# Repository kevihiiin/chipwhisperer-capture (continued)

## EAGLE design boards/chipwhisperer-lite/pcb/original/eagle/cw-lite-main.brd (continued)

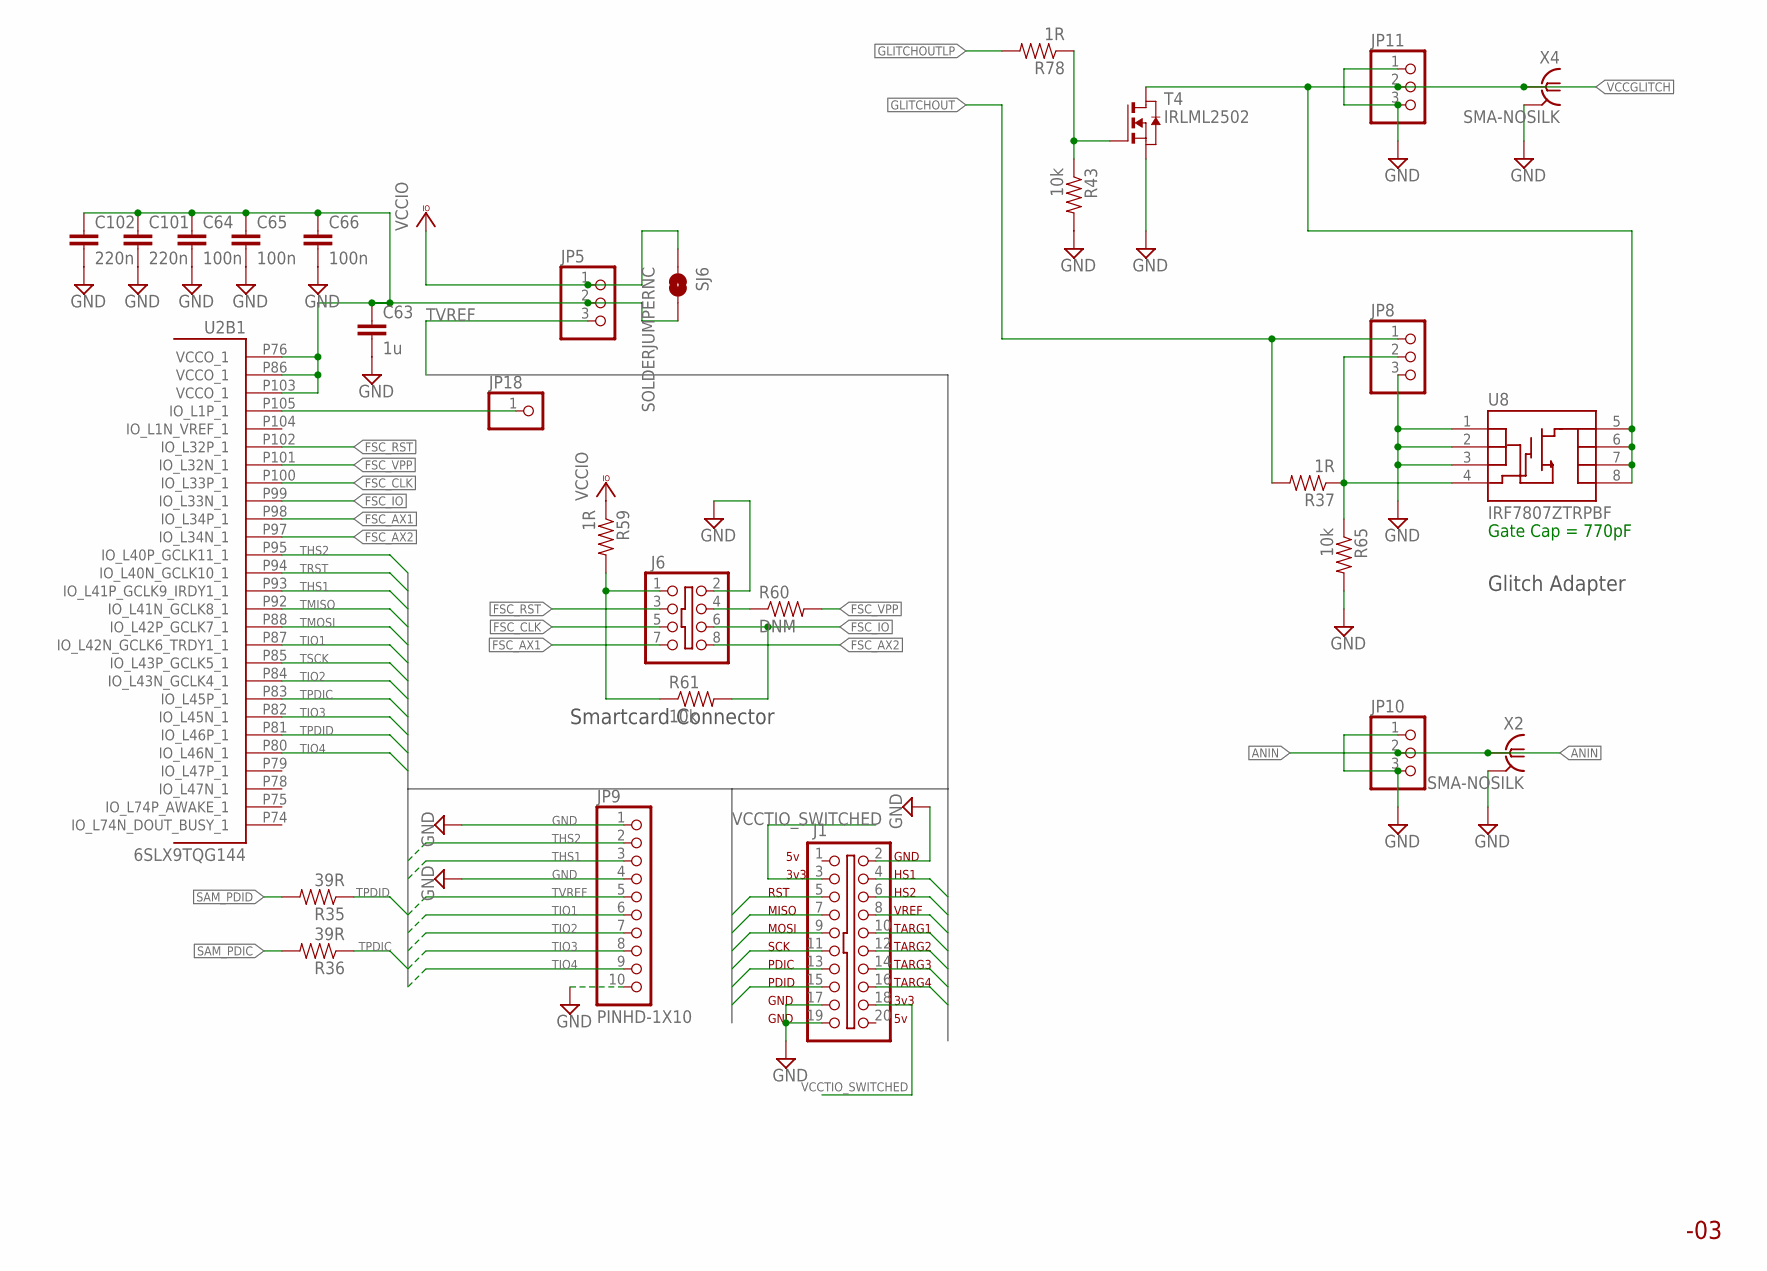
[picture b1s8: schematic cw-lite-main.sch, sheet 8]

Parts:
C63: 1u; 0603C
C64, C65, C66: 100n; 0402C
C101, C102: 220n; 0402C
J1: SHROUD_2X10-SHROUDED; PINSHRD_PTH_2X10
J6: SHROUD_2X4SHROUD; PINSHRD_PTH_2X04
JP5, JP8, JP10, JP11: PINHD-1X3; 1X03
JP9: PINHD-1X10; 1X10-BIG
JP18: PINHD-1X1; 1X01
R35, R36: 39R; 0603R
R37, R59, R78: 1R; 0603R
R43, R61, R65: 10k; 0603R
R60: DNM; 0603R
SJ6: SOLDERJUMPERNC; SJ_2S
T4: IRLML2502; SOT-23; MPN IRLML2502TRPBF
U2: 6SLX9TQG144; TQ144; MPN XC6SLX9-3TQG144C
U8: IRF7807ZTRPBF; SO08
X2, X4: SMA-NOSILK; J502-ND-142-0711-821/826-NOSILK

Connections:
ANIN: JP10.2, X2.1; also elsewhere on the board
FSC_AX1: J6.7, U2.P98 (IO_L34P_1)
FSC_AX2: J6.8, U2.P97 (IO_L34N_1)
FSC_CLK: J6.5, U2.P100 (IO_L33P_1)
FSC_IO: J6.6, R61.2, U2.P99 (IO_L33N_1)
FSC_RST: J6.3, U2.P102 (IO_L32P_1)
FSC_VPP: R60.2, U2.P101 (IO_L32N_1)
GLITCHOUT: JP8.1, R37.2; also elsewhere on the board
GLITCHOUTLP: R78.2; also elsewhere on the board
GND: C63.2, C64.2, C65.2, C66.2, C101.2, C102.2, J1.2, J1.17, J1.19, J6.2, JP8.3, JP9.1, JP9.4, JP9.10, JP10.1, JP10.3, JP11.1, JP11.3, R43.2, R65.2, T4.2 (S), U8.1 (S), U8.2 (S), U8.3 (S), X2.G@1 (2), X2.G@2 (2), X2.G@3 (2), X2.G@4 (2), X4.G@1 (2), X4.G@2 (2), X4.G@3 (2), X4.G@4 (2); also elsewhere on the board
unnamed: JP8.2, R37.1, R65.1, U8.4 (G)
unnamed: JP18.1, U2.P105 (IO_L1P_1)
unnamed: R43.1, R78.1, T4.3 (G)
unnamed: J6.1, R59.2, R61.1
unnamed: J6.4, R60.1
SAM_PDIC: R36.2; also elsewhere on the board
SAM_PDID: R35.2; also elsewhere on the board
TARGET_VCCIO: C63.1, C64.1, C65.1, C66.1, C101.1, C102.1, JP5.2, SJ6.2, U2.P76 (VCCO_1), U2.P86 (VCCO_1), U2.P103 (VCCO_1)
THS1: J1.4, JP9.3, U2.P93 (IO_L41P_GCLK9_IRDY1_1); also elsewhere on the board
THS2: J1.6, JP9.2, U2.P95 (IO_L40P_GCLK11_1); also elsewhere on the board
TIO1: J1.10, JP9.6, U2.P87 (IO_L42N_GCLK6_TRDY1_1); also elsewhere on the board
TIO2: J1.12, JP9.7, U2.P84 (IO_L43N_GCLK4_1); also elsewhere on the board
TIO3: J1.14, JP9.8, U2.P82 (IO_L45N_1); also elsewhere on the board
TIO4: J1.16, JP9.9, U2.P80 (IO_L46N_1); also elsewhere on the board
TMISO: J1.7, U2.P92 (IO_L41N_GCLK8_1); also elsewhere on the board
TMOSI: J1.9, U2.P88 (IO_L42P_GCLK7_1); also elsewhere on the board
TPDIC: J1.13, R36.1, U2.P83 (IO_L45P_1); also elsewhere on the board
TPDID: J1.15, R35.1, U2.P81 (IO_L46P_1); also elsewhere on the board
TRST: J1.5, U2.P94 (IO_L40N_GCLK10_1); also elsewhere on the board
TSCK: J1.11, U2.P85 (IO_L43P_GCLK5_1); also elsewhere on the board
TVREF: J1.8, JP5.3, JP9.5; also elsewhere on the board
VCCGLITCH: JP11.2, T4.1 (D), U8.5 (D), U8.6 (D), U8.7 (D), U8.8 (D), X4.1; also elsewhere on the board
VCCIO: JP5.1, R59.1, SJ6.1; also elsewhere on the board
VCCTIO_SWITCHED: J1.3, J1.18; also elsewhere on the board

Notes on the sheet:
HS1
HS2
VREF
TARG1
TARG2
TARG3
TARG4
3v3
RST
MISO
MOSI
SCK
PDIC
PDID
GND
Glitch Adapter
Smartcard Connector
Gate Cap = 770pF

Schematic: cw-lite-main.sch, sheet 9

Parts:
C37: 47u; 0805
C103: 10u; 0603C
C104: 10n; 0603C
C105, C107: 1u; 0603C
C106, C108, C109: 100n; 0603C
C115, C116, C121: DNM; 0603C
C118, C119, C120: CAP0603-CAP; 0603C
J2: SHROUD_2X10-SHROUDED; PINSHRD_PTH_2X10
J9: 2171790001; MOLEX_2171790001
JP6, JP7, JP12: PINHD-1X2; 1X02
JP13: PINHD-1X9; 1X09-BIG
JP14, JP15, JP16, JP17: PINHD-1X1; 1X01
L10: 1k/500mA; FB603
LED9, LED10: LED-0603; LED-603
Q2: CRYSTALHC49U-V; HC49U-V
R13: 10k; 0603R
R66, R76: 49R9; 0805
R67, R72: 100R; 0603R
R73: DNM; 0603R
R74, R75: 1k; 0603R
R83, R84: 5k1; R0402
SJ2: SOLDERJUMPER_2WAYPASTE2&3; SJ_3_PASTE2&3
SJ3, SJ4, SJ5, SJ7: SOLDERJUMPERNC; SJ_2S
U11: V_REG_MIC2920; SOT223
U12: XMEGA128A4U; TQFP44; MPN ATXMEGA128A4U-AU
X3, X5: SMA-NOSILK; J502-ND-142-0711-821/826-NOSILK

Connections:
ANIN: JP7.2, SJ4.2, X3.1; also elsewhere on the board
GND: C37.2, C103.2, C104.2, C105.2, C106.2, C107.2, C108.2, C109.1, C115.2, C116.1, C118.1, C119.1, C120.1, C121.1, J2.2, J2.17, J2.19, J9.A1B12 (GND), J9.B1A12 (GND), JP13.9, R83.1, R84.1, U11.2 (GND), U12.8 (GND), U12.18 (GND1), U12.30 (GND2), U12.38 (GND3), X3.G@1 (2), X3.G@2 (2), X3.G@3 (2), X3.G@4 (2), X5.G@1 (2), X5.G@2 (2), X5.G@3 (2), X5.G@4 (2); also elsewhere on the board
unnamed: C118.2, J9.SH1 (SHLD), J9.SH2 (SHLD), J9.SH3 (SHLD), J9.SH4 (SHLD)
unnamed: C107.1, C108.1, C109.2, JP12.1, R66.2, SJ3.2, U12.39 (AVCC)
unnamed: C121.2, JP6.1, JP7.1, R66.1, SJ4.1, SJ5.1, U12.9 (VCC), U12.19 (VCC1), U12.31 (VCC2)
unnamed: C119.2, J9.A4B9 (VBUS), J9.B4A9 (VBUS), U11.1 (IN)
unnamed: C120.2, SJ2.1, U11.3 (OUT)
unnamed: LED9.A, R74.1
unnamed: LED10.A, R75.1
unnamed: LED9.C, U12.1 (PA5)
unnamed: LED10.C, U12.2 (PA6)
unnamed: JP13.1, U12.25 (PD5)
unnamed: JP13.2, U12.24 (PD4)
unnamed: JP13.3, U12.23 (PD3)
unnamed: JP13.4, U12.22 (PD2)
unnamed: JP13.5, U12.21 (PD1)
unnamed: C115.1, Q2.2, R72.1, U12.37 (PR1(XT1))
unnamed: C116.2, Q2.1, R73.1, U12.36 (PR0(XT2))
unnamed: R67.2, U12.7 (PB3)
unnamed: JP13.6, U12.20 (PD0)
unnamed: L10.2, R76.2
unnamed: J9.B5 (CC2), R84.2
unnamed: J9.A5 (CC1), R83.2
unnamed: C37.1, C105.1, C106.1, JP12.2, R76.1, SJ3.1
THS1: J2.4, R67.1; also elsewhere on the board
THS2: J2.6, R72.2, R73.2; also elsewhere on the board
TIO1: J2.10, JP16.1, U12.13 (PC3); also elsewhere on the board
TIO2: J2.12, JP17.1, U12.12 (PC2); also elsewhere on the board
TIO3: J2.14, JP14.1, U12.41 (PA1); also elsewhere on the board
TIO4: J2.16, JP15.1, U12.40 (PA0); also elsewhere on the board
TMISO: J2.7; also elsewhere on the board
TMOSI: J2.9; also elsewhere on the board
TPC6: JP13.8, U12.16 (PC6)
TPC7: JP13.7, U12.17 (PC7)
TPDIC: J2.13, R13.2, U12.35 (!RESET!/PDI_CLK); also elsewhere on the board
TPDID: J2.15, U12.34 (PDI_DATA); also elsewhere on the board
TRST: J2.5; also elsewhere on the board
TSCK: J2.11; also elsewhere on the board
TUSB_N: J9.A6 (D+), J9.B6 (D+), U12.26 (PD6)
TUSB_P: J9.A7 (D-), J9.B7 (D-), U12.27 (PD7)
TVREF: J2.8, SJ7.2; also elsewhere on the board
VCCGLITCH: JP6.2, SJ5.2, X5.1; also elsewhere on the board
VCCTIO_SWITCHED: J2.3, J2.18, SJ2.3; also elsewhere on the board
VCC_TARG: C103.1, C104.1, L10.1, R13.1, R74.2, R75.2, SJ2.2, SJ7.1

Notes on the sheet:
Breakaway Section of PCB
Might be XMEGA128D3 instead?

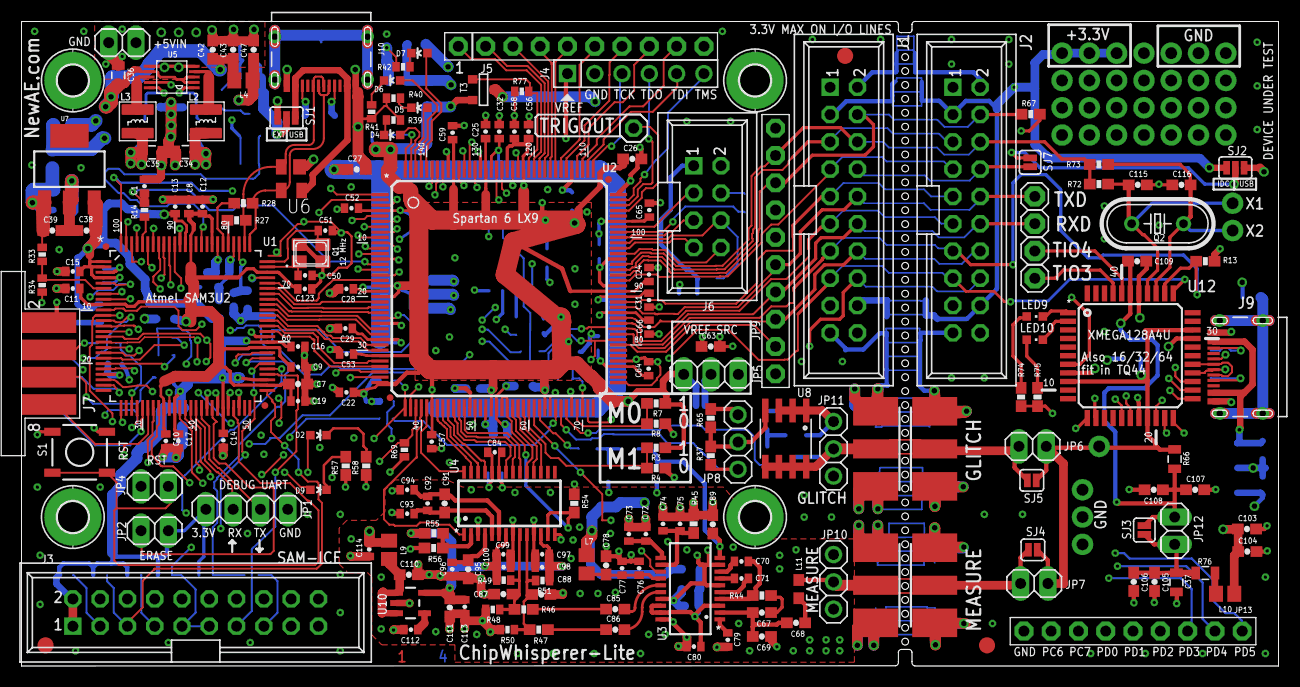
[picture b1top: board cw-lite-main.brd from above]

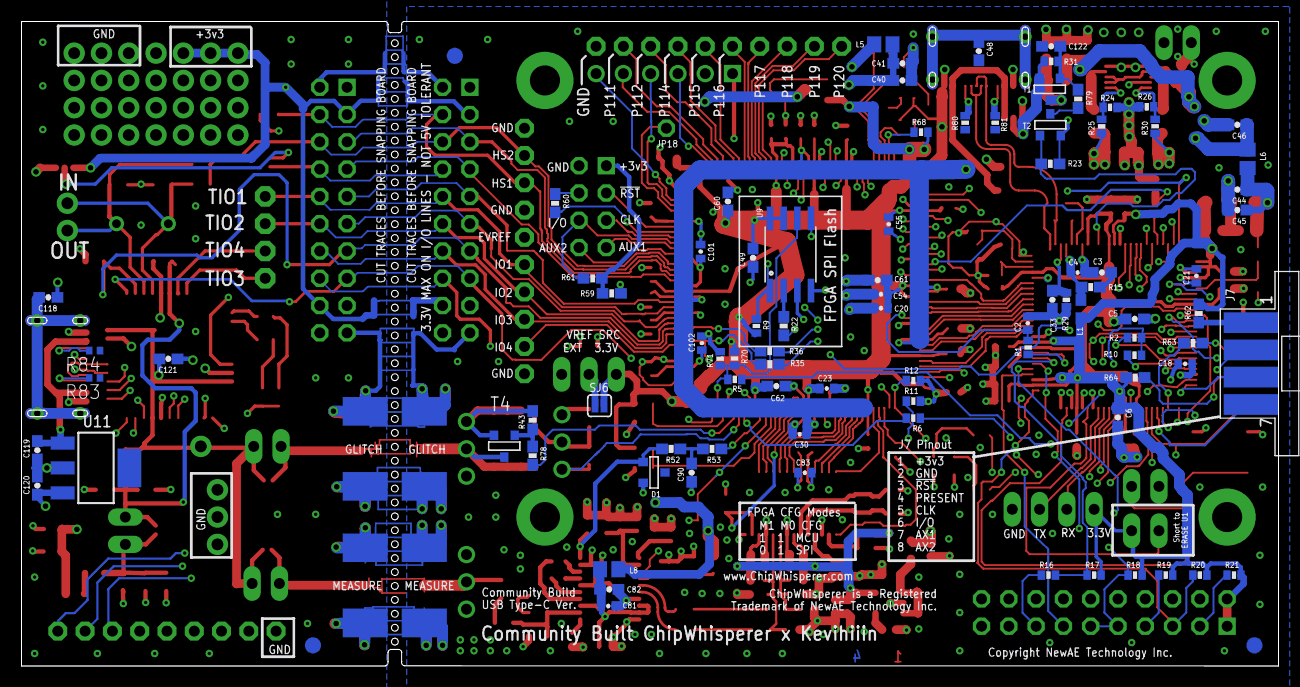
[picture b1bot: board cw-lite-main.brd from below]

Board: 4 copper layers, 117.0 x 60.0 mm, 294 parts (91 on the bottom side), 227 nets.

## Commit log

2023-11-22 Add naeusb to nano firmware
2023-11-29 Add builds for firmware
2023-11-29 Fix action path
2023-11-29 Fix identifier
2023-12-11 Add openadc
2023-12-11 Fix paths for openadc
2024-08-13 fix nano/lite build
2024-08-13 update gitmodules
2025-08-29 Swap to USB-C connector on main board
2025-08-30 Change to Molex connector and clean up layout
2025-08-30 Swap to USB-C connector on target board
2025-08-30 Fix silkscreen: USB-C, Community Text
